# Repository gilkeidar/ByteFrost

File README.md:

# ByteFrost 

The Breadboard 8-bit CPU and Computer

Be sure to check out the [YouTube channel](https://www.youtube.com/@bytefrost) for more in-depth explanations of how the ByteFrost works!

*ByteFrost under development*

In this Github repository are software tools for using the ByteFrost computer:

## Assembler
Assembler program that converts Assembly code to ByteFrost machine language.

**Note:** The `Assembler/` directory contains the deprecated assembler;
`Assembler V2/` contains the new assembler, which also has new preprocessing
features, assembly instructions that can be translated to multiple ISA
instructions, and support for the new 16-bit memory address space expansion.

## Display
Arduino code for the ByteFrost's display card (an Arduino Nano) for a 2004A LCD display.

## Disk
Arduino code for the ByteFrost's disk controller (an Arduino MKR Zero) for a
micro SD card that serves as the ByteFrost's disk.

Also included is software for handling ByteFrost disk files using the ByteFrost
FileSystem (BFSv1), a very rudimentary filesystem with one root directory.

## Documentation
Documentation for the ByteFrost computer. Includes hardware documentation (i.e. schematics) and software documentation (instruction set specifications, control signal lists, each instruction's micro-code and structure, and assembly syntax). For more documentation, see the [wiki](https://github.com/gilkeidar/ByteFrost/wiki).

## Microcode
Arduino code for programming the three microcode EEPROMs (using Ben Eater's [EEPROM programmer](https://github.com/beneater/eeprom-programmer/blob/master/eeprom-programmer/eeprom-programmer.ino) as a basis).

## Programs
Programs written in ByteFrost assembly that can be compiled using the assembler and run on the ByteFrost computer. Each program comes with the assembly code (`.asm` file), machine language compilation (`.mlg` file), and a binary file (`.bin` file).

##  Credits

The ByteFrost is a 2-person father-son project (by Gil and Ron Keidar) that we 
have been working on on-and-off (mostly during vacation between university 
quarters) for a few years (since March 2022).

My (Gil's) idea behind creating the ByteFrost was to work on a project that
covers many abstraction layers in computer science (all of the way from the
discrete logic layer to the application layer) and to, in the process, learn
about and get hands-on experience with those layers.

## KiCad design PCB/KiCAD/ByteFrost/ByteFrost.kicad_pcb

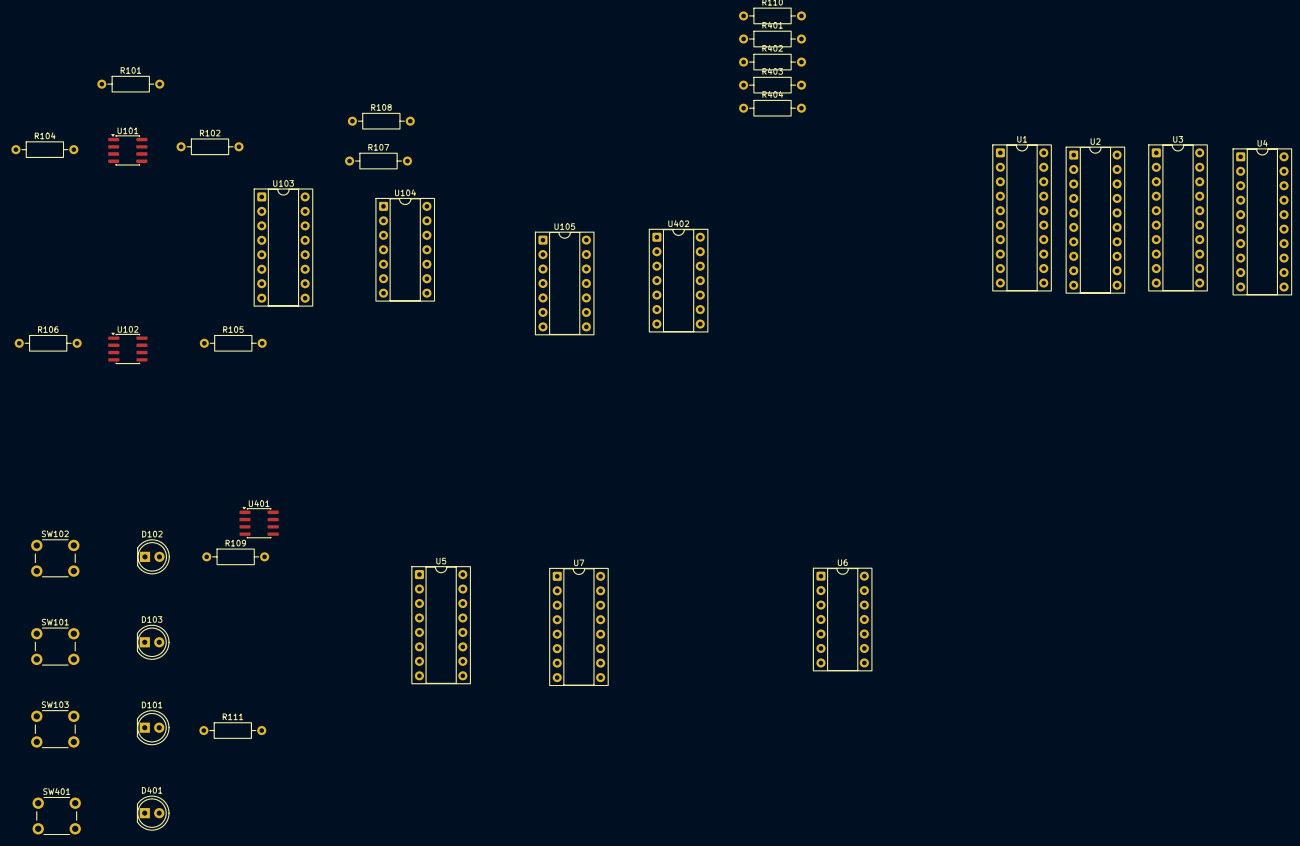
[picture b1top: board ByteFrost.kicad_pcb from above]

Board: 2 copper layers, 36 parts (0 on the bottom side), 50 nets, no tracks yet.

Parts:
D101: LED (green); LED_D5.0mm
D102, D401: LED (red); LED_D5.0mm
D103: LED (blue); LED_D5.0mm
R101, R107, R108: 10K; R_Axial_DIN0207_L6.3mm_D2.5mm_P10.16mm_Horizontal
R102: 100; R_Axial_DIN0207_L6.3mm_D2.5mm_P10.16mm_Horizontal
R104: 212K; R_Axial_DIN0207_L6.3mm_D2.5mm_P10.16mm_Horizontal
R105: 20K; R_Axial_DIN0207_L6.3mm_D2.5mm_P10.16mm_Horizontal
R106, R109, R110, R111, R401, R404: 5.1K; R_Axial_DIN0207_L6.3mm_D2.5mm_P10.16mm_Horizontal
R402: 17K; R_Axial_DIN0207_L6.3mm_D2.5mm_P10.16mm_Horizontal
R403: 51K; R_Axial_DIN0207_L6.3mm_D2.5mm_P10.16mm_Horizontal
SW101: Single_Step; SW_PUSH_6mm_H7.3mm
SW102: Break; SW_PUSH_6mm_H7.3mm
SW103: Cont.; SW_PUSH_6mm_H7.3mm
SW401: Reset; SW_PUSH_6mm_H7.3mm
U1, U2, U3, U4: 74HC374; DIP-20_W7.62mm_Socket
U5: 74HC139; DIP-16_W7.62mm_Socket
U6: 74HC02; DIP-14_W7.62mm_Socket
U7: 74HC153; DIP-16_W7.62mm_Socket
U101, U102, U401: ICM7555xB; SOIC-8_3.9x4.9mm_P1.27mm
U103: 74HC76; DIP-16_W7.62mm_Socket
U104: 74HC32; DIP-14_W7.62mm_Socket
U105: 74HC00; DIP-14_W7.62mm_Socket
U402: 74HC14; DIP-14_W7.62mm_Socket

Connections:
2sec_Reset: U103.2 (~S), U105.6, U105.9
+5V: R104.1, R105.1, R106.1, R401.1, R402.1, R403.1, SW102.1, SW103.1, U1.20 (VCC), U2.20 (VCC), U3.20 (VCC), U4.20 (VCC), U5.16 (VCC), U6.14 (VCC), U7.16 (VCC), U101.4 (~RST), U101.8 (VCC), U102.4 (~RST), U102.8 (VCC), U103.5 (VCC), U104.14 (VCC), U105.14 (VCC), U401.4 (~RST), U401.8 (VCC), U402.14 (VCC)
CLK: D103.2 (A), U6.3, U6.6, U6.9, U6.12, U105.8
DATA0: U1.2 (O0), U1.3 (D0), U2.2 (O0), U2.3 (D0), U3.2 (O0), U3.3 (D0), U4.2 (O0), U4.3 (D0)
DATA1: U1.4 (D1), U1.5 (O1), U2.4 (D1), U2.5 (O1), U3.4 (D1), U3.5 (O1), U4.4 (D1), U4.5 (O1)
DATA2: U1.6 (O2), U1.7 (D2), U2.6 (O2), U2.7 (D2), U3.6 (O2), U3.7 (D2), U4.6 (O2), U4.7 (D2)
DATA3: U1.8 (D3), U1.9 (O3), U2.8 (D3), U2.9 (O3), U3.8 (D3), U3.9 (O3), U4.8 (D3), U4.9 (O3)
DATA4: U1.12 (O4), U1.13 (D4), U2.12 (O4), U2.13 (D4), U3.12 (O4), U3.13 (D4), U4.12 (O4), U4.13 (D4)
DATA5: U1.14 (D5), U1.15 (O5), U2.14 (D5), U2.15 (O5), U3.14 (D5), U3.15 (O5), U4.14 (D5), U4.15 (O5)
DATA6: U1.16 (O6), U1.17 (D6), U2.16 (O6), U2.17 (D6), U3.16 (O6), U3.17 (D6), U4.16 (O6), U4.17 (D6)
DATA7: U1.18 (D7), U1.19 (O7), U2.18 (D7), U2.19 (O7), U3.18 (D7), U3.19 (O7), U4.18 (D7), U4.19 (O7)
GND: R101.2, R107.2, R108.2, R109.2, R110.2, R111.2, R404.2, SW101.1, SW401.1, U1.10 (GND), U2.10 (GND), U3.10 (GND), U4.10 (GND), U5.8 (GND), U6.7 (GND), U7.1 (Ea), U7.8 (GND), U7.15 (Eb), U101.1 (GND), U102.1 (GND), U103.13 (GND), U104.7 (GND), U105.7 (GND), U401.1 (GND), U402.7 (GND)
INSTR6: U5.14 (A0), U7.3 (I3a), U7.4 (I2a)
INSTR7: U5.13 (A1), U7.12 (I2b), U7.13 (I3b)
unnamed: R403.2, U402.1
unnamed: D101.2 (A), U103.15 (Q), U104.1
unnamed: D101.1 (K), R111.1
unnamed: D102.2 (A), U103.14 (~Q), U104.4
unnamed: D102.1 (K), R109.1
unnamed: D103.1 (K), R110.1
unnamed: D401.2 (A), U105.4, U105.5, U401.3 (OUT)
unnamed: D401.1 (K), R404.1
unnamed: U1.11 (Cp), U6.1
unnamed: U1.1 (OE), U5.4 (O0)
unnamed: U2.11 (Cp), U6.4
unnamed: U2.1 (OE), U5.5 (O1)
unnamed: U3.11 (Cp), U6.10
unnamed: U3.1 (OE), U5.6 (O2)
unnamed: U4.11 (Cp), U6.13
unnamed: U4.1 (OE), U5.7 (O3)
unnamed: U5.12 (O0), U6.2
unnamed: U5.11 (O1), U6.5
unnamed: U5.10 (O2), U6.8
unnamed: U5.9 (O3), U6.11
unnamed: R101.1, U101.5 (CONT)
unnamed: R102.2, U101.3 (OUT), U103.1 (C), U104.5
unnamed: R104.2, U101.2 (TRIG), U101.6 (THRES)
unnamed: R105.2, U102.6 (THRES), U102.7 (DISCH)
unnamed: U102.3 (OUT), U104.2
unnamed: R106.2, SW101.2, U102.2 (TRIG)
unnamed: R107.1, SW103.2, U103.4 (J)
unnamed: R108.1, SW102.2, U103.16 (K)
unnamed: U104.3, U105.2
unnamed: U104.6, U105.1
unnamed: U105.3, U105.10
unnamed: R402.2, U401.6 (THRES), U401.7 (DISCH)
unnamed: R401.2, SW401.2, U401.2 (TRIG)
unnamed: U402.2, U402.3
R.O_Select_High: U5.3 (A1), U7.9 (Zb)
R.O_Select_Low: U5.2 (A0), U7.7 (Za)

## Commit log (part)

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2022-04-10 Initial commit
    Created file I/O code for assembler (creates empty output file, doesn't convert any assembly yet)
2022-05-04 First version (parsing + output)
    First basic version - parses file and produces output file for a few opcodes.
2022-05-05 Updated Design
2022-05-08 Add error report and exit if does not recognize input. Also handle lines with zero tokens (empty lines or comment only )
2022-05-09 Added binary flag and changed a constant definition
2022-05-19 Add short ALU and Branch Absolute commands
2022-05-19 Dump SRAM memory to display
2022-06-21 Minor changes to assembler + new instructions (INC / DEC)
2022-06-21 Small fix
2022-06-21 Changed file name to README
2022-06-21 Added Program README and cleaned memdump
2022-06-21 Removed test files
2022-06-22 Added relative branches to assembler
    Added relative branching to assembler with a new instruction parameter type, "branch_amt"
2022-06-22 add bist
2022-06-23 Add the Arduino Display Driver
2022-06-23 Cosmetic changes to instruction.h
2022-06-23 Adding exe file
2022-06-23 Added compiled versions of BIST and memdump
2022-06-25 BIST fixes
2022-06-25 Assembler update and bug fix
    Updated assembler to print instruction line in mlg file (absolute branching goes awry if there are lines without instructions - assembler makes program counter go to those lines, even though they do 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
2022-06-25 print statement in eight queens
2022-06-25 Updated eight queens
2022-06-26 bugfix eight queens
2022-06-26 Added version of eight queens with all solutions
2022-07-03 Improved display code
    Display is still the bottleneck, but can more or less safely reach ~100 kHz clock
2022-07-05 HW INT for Display Driver
    Add Register to hold display output,
    Add note to explain R on pin 5 of 555
    Update the PPT
2022-07-18 Update CPU.pptx
    Fixed incorrect instruction structure for RTS instruction (no 8-bit immediate is in the instruction)
2022-07-19 Updated recursive fibonacci
    Removed printouts of current input parameter n and replaced it with a static counter of the number of function calls
2022-07-30 Display fix, powerpoint update, and BIST update
2022-08-26 Debugging BST implementation
2022-08-26 BST debug continues
2022-08-28 Small fix to assembler
2022-08-29 Update to BST
2022-08-29 BST fix
2022-08-29 Cleaned up BinarySearchTree folder
2022-08-29 Added microcode for Test / compare instructions
2022-08-30 Modification to BST attempt with new COMP instruction
2022-09-06 Added simple demo program (5 NOPs and BRK)
2022-09-06 basic operation, animated
2023-12-26 Slight changes to documentation + new disk folder for SD card
2023-12-29 Updated documentation
2024-02-08 Shift Register commands
    Add test to read Shift Register commands
2024-02-19 Update CPU.pptx
    Reordering slides, adding High-Level section at the beginning
2024-03-05 Applied small fixes to powerpoint documentation
2024-03-11 Small fixes to CPU documentation powerpoint
2024-03-19 Update CPU.pptx
    Adding first slides to v2.0 including sharing the buses during fetch instruction
2024-07-30 Update CPU.pptx
    Added a note that LSB in the address is coming from the PC Advance and is using some bit in the higher 245 but lands in bit 0 of the address bus
2024-08-09 Updated assembler + added new instruction
    Added new LSP imm (Load Special Register) instruction to load high byte of PC, Data Pointer, or Stack Pointer (part of expansion into 16 bit addressing)
2024-08-30 Update CPU.pptx
    More details
2024-09-02 LSP and migration to AMAP
    Add assembler support to Load Special Pointer LSP. Fix 8Queens to use LSP to enable use the RAM according to the AMAP. Convert it to labels.,
2024-09-07 Updaed RTS instr to suport 16-bit jump
2024-09-08 Added RAM test program and more ALU imm instructions
2024-09-09 Initial Visual Studio C++ project setup
2024-09-15 Initial work, setting up directories and initial work on CLAP
2024-09-15 Updated CLAP design document
2024-09-17 Added error for invalid token encountered in input .asm file parsing
2024-09-18 Finished inital implementation of Parser (without being able to generate preprocessor directive lines nor label definition lines yet)
2024-09-20 More general implementation of AssemblyInstruction's generateCode() method
2024-09-20 Added partial assembly as structs
2024-09-23 Added argument range checking for ISAInstructions and AssemblyInstructions (if a given immediate value doesn't fit in an ISAInstruction's argument (as determined by the ExpectedArgument's size and Ar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
2024-09-24 Initial preprocessor implementation; constants may be up to 8 bytes in size (using long long as sizeof(long long) = 8) Added .define directive
2024-09-25 Added OUT_PRINT_TYPE TokenType and more assembly instructions (up to OUT Rs1, A/I)
2024-09-25 Hack to add special register support, a few more instructions added and first attempt at compiling eight queens
2024-09-30 In-progress adding documentation, cleaning code, adding comments; added optimization that lines vector isn't copied when returned from the parser, rather the parser fills an existing Line * vector in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
2024-11-09 Update doc slides
    Update doc slides
    MMIO test
2024-11-19 Add logic analyzer to PPT
2024-11-21 New MMIO Device (32-bit cycle counter)
    Updated documentation + added example program
2025-01-10 New laptop
    New laptop
2025-01-11 Update CPU v2.0.pptx
    Update MMIO Bus arbitration
2025-01-13 SD Card Bus release working
    SD Card Bus release working
2025-01-13 Initial implementation of reading sector from SD card
2025-01-13 Disk_v2.ino update
2025-01-14 Updated Disk Driver Arduino
    First implementation of being able to write a page from the ByteFrost RAM to a sector in the disk.
2025-02-24 Increased performance by > 1000%
2025-02-24 included binary files
2025-02-26 Cleaning assembler cruft
2025-05-15 Documentation updates
2025-05-15 Added ls program + update other program
2025-05-28 Updated Addressing Modes Instruction Architecture Documentation
    + Added a slide regarding the ByteFrost's instruction decode logic
2025-05-31 Fixed small bug in Arduino disk controller regarding writing to disk + RNG program
    With bug fix, writing to disk appears to work correctly + added RNG program using new TRNG device.
2025-06-10 More work towards new addressing modes architecture proposal
2025-06-16 EEPROM LUT Generator code added + addressing modes proposal documentation
2025-07-13 Updated new proposal documentation + added microcode for all new / updated instructions
2025-07-13 Updated slides, working on new roadmap document
2025-07-13 Further updates
2025-07-13 Updated doc + changed OPCODE_MAG_LDW_SDW_MAA to be active high (ARSelect)
2025-07-13 Update CPU v2.0.pptx
    Replace many ANDs with one 8-bin NOR - slide 55
2025-11-26 Documentation updates for addressing modes proposal
2025-11-27 New LDW microcode
2025-11-29 Added SDW instruction support
    SDW assembler support + microcode + test program (hopefully bug-free but includes instruction counting which may be incorrect)
2025-11-29 Delete CPU v2.0.pptx
    Add AR Select Slide
2025-11-29 Archive old versions
    Archive old versions
2025-11-29 fix pptx
2025-11-30 Add TmpAR slide
2025-11-30 Updated AR DB LE LUT to include main clock signal
    Using main clock signal as an additional input to the AR DB LE LUT to avoid having to NOR the active low load triggers (effectively including the NOR clock-gating logic as part of the LUT).
2025-11-30 Removed LSP, added LDA
    Updated LDW_SDW test to use LDA instruction instead of LSP (note that currently LDA can't load to SP so LDA %SP, H, #0x32 won't do anything, but this is a transient state of the HW and will soon be f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
2025-12-04 Fixing include path
    Fixing include path
2025-12-04 Add some values to stack pointer high and check them
2025-12-18 replaced another find_first_of with find_last_of
2025-12-21 make sure ppt is uptodate
2025-12-23 Update CPU v2.0.pptx
    Update slides, list of Op codes, hide old op codes
2025-12-25 Updated documentation + LDW SDW test
2025-12-26 Update microcode.ino
    Fix attempt - weird bug when fetching commit on other computer
2025-12-26 Added MGA instruction support
2025-12-26 Update Stack Pointer Diagram
    Update Stack Pointer Diagram
2025-12-26 Added support for the MAA instruction
    microcode + assembly support
2025-12-27 Fix for AR DB LE LUT
2025-12-28 Add TST and use it in BIST for NOP counter
2025-12-29 BIST coverage of ALU Op2 complete
2025-12-30 Updated NOP and BRK to be single-cycle instructions
    More accurately: 3cycles (2 to fetch, 1 to execute)
    In a sequence of NOPs, we can observe that the first NOP takes 3 cycles and the rest take only 2:
    NOP 1 | NOP 2 | NOP 3 ...
    NOP fetch L | NOP fetch H | NOP exec = NOP fetch L | NOP fetch H | NOP exec = NOP fetch L | ...
2026-01-02 Finished converting 8 Queens to the new address registers
    Replaced LMR/SMR/LMA/SMA/LSP deprecated commands with new ones
    Added counter to report total number of clocks
    Added a flow diagram to the code
2026-01-02 Boot ROM code + Initial ls -ls implementation (BFSv1)
2026-01-05 Finish BIST ALU Immediate
2026-01-07 ls -ls fully working
    Tested at full clock speed
2026-01-08 Abb MAG MGA test to BIST
2026-01-09 Changed PL LD Branch to "Active High' Replaced the NAND generating it with an AND
    The NAND was of type 'LS' and I suspected it is generating glitch as the voltage is too low for LS. for type 'HC' I had only AND and not NAND so i took the opportunity to change the level in the LUT 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
2026-01-11 Extend Bistv3 to cover SP in MAG/MGA
    (In addition, the Disk INO contains printout on boot and printout the command (read/write)
2026-01-13 Added a plan to free up a tx pin for tty display
2026-01-16 Update Display.ino
    Back to the original code. Clean up.
2026-01-16 Update CPU v2.0.pptx
    Made Display slides accurate, added notes
2026-01-18 Partial dev log updates
2026-01-18 Updated development logs
2026-01-19 Update mmio.asm
    Refresh commands. Cover SD Card, RNG, Counter, and just touch the other MMIO slots
2026-01-20 Added null terminator as special character
2026-01-22 Full migration to the new stack pointer
    reverse SP L LUT polarity , it is now active high (both L and H are inversed before the chip but they are consider active high to use the local AND with the negative clock.
    BIST is enhanced to test SP and report more failures
2026-01-24 First shell
2026-02-09 invert data clock on KBD signal out
2026-02-20 Update CPU v2.0.pptx
    Add
    1. Delay on #OE
    2. Quiesce on #OE and #WE
    3. Remove work-around of gating the keyboard with SRAM Load (the delay of #OE solved the glitches on that signal)
2026-02-20 Updated shell prompt
2026-02-20 Fix prompt
2026-02-20 Shell fix
2026-02-20 Fixed shell
2026-04-11 old unsaved work..
2026-04-12 Fix bug in RTS
    Fix bug in RTS , avoid changing SP while using it. (made the command 6 clocks instead of 4)
    First JSR-RTS works in SHELL
    The Shell first command "list memory" works as a stub. The next step is to build a lib function ATOI to convert the user input address to hexadecimal value.
2026-04-15 Improve BIST LDW to address HW bug it did not detect
2026-04-20 build_assembpler command line compile and copy the assembler
2026-04-23 Added BIST coverage for TST, separate PC in SW from PC in HW
    PC in HW points to instruction.
    PC in SW points to address.
    So when PC is read, it is shifted left one bit, and when written it is shifted write one bit.
2026-05-14 CALL-RTS works!
    CALL-RTS works! Tested with recursion depth of 6 with mixed with PUSH & POP
2026-05-18 BISTv3 is complete
    Added coverage for MAA and LDA
2026-05-22 Start study PCB production
    Using KiCAD: Did the Register File
2026-05-23 BootROM run BIST and loads SD Card
    Now need to fix the code in the SD to run Shell
2026-05-23 move directories
2026-05-29 Finish KiCAD Clock and Reset
